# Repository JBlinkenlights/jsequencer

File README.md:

# jsequencer
A small 16-step midi sequencer based on the Teensy 3.1.  It currently features note editing and tempo tap.

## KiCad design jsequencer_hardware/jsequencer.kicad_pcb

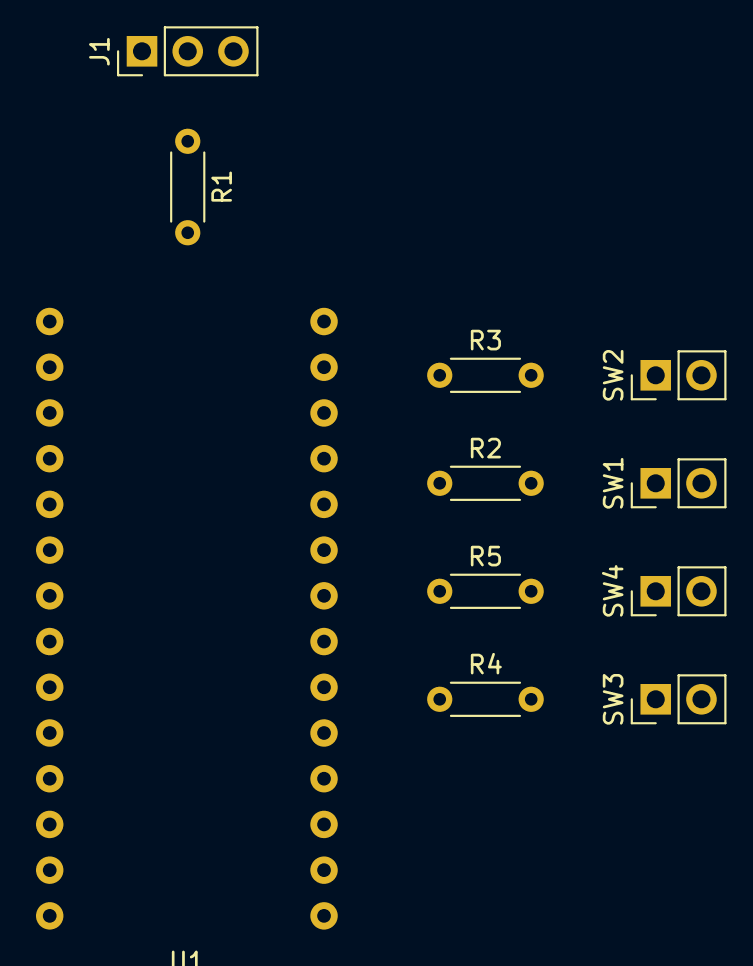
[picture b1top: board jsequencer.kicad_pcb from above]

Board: 2 copper layers, 11 parts (0 on the bottom side), 8 nets, no tracks yet.

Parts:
J1: Conn_01x03_Male; PinHeader_1x03_P2.54mm_Vertical
R1: 470; R_Axial_DIN0204_L3.6mm_D1.6mm_P5.08mm_Horizontal
R2, R3, R4, R5: 10K; R_Axial_DIN0204_L3.6mm_D1.6mm_P5.08mm_Horizontal
SW1, SW2, SW3, SW4: SW_Push_Dual; PinHeader_1x02_P2.54mm_Vertical
U1: Teensy_3_1; teensy_3_1

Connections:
+5V: J1.3, R2.1, R3.1, R4.1, R5.1, U1.27
unnamed: J1.2, R1.1
unnamed: R2.2, SW1.1
unnamed: R3.2, SW2.1
unnamed: R4.2, SW3.1
unnamed: R5.2, SW4.1
Teensy_Pin_0: J1.1, SW1.2, SW2.2, SW3.2, SW4.2, U1.1, U1.2, U1.3, U1.4
Teensy_Pin_10: R1.2, U1.12

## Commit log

2019-12-03 Made README a bit clearer.
2019-12-03 Added source code and KiCad project files.
2020-01-28 Improved tempo tap and UI.
2020-01-28 Refactor entire repo. Commit all the latest software.
2020-01-28 Add to README
